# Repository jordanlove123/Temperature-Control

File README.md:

# Temperature Control
System for controlling temperature of an object to within 10 mK of a given setpoint.

DISCLAIMER: As is discussed below, some parts of the system will have to be designed by the user because they depend on the shape, size, and thermal mass of the object. This means that to a certain extent, performance is dependent on the user's design of these components, but I tried to include as many recommendations as possible for best practices.

## Setup

### Recommended installations
Before starting setup, there is software that is necessary to access some of the files in this repository:
* [Arduino IDE](https://www.arduino.cc/en/software/): Edit and upload Arduino code
* [KiCAD](https://www.kicad.org/download/): View and export PCB files
* [Prusa Slicer](https://www.prusa3d.com/page/prusaslicer_424/): Convert STL 3D models to gcode for a 3D printer
* [Realterm](https://sourceforge.net/projects/realterm/): Send serial commands and save serial data from Arduino to text file

These programs can all be downloaded for free.

### Manufacturing

#### Shield PCB
The PCB files can be found at [Manufacturing/Shield PCB](Manufacturing/ShieldPCB/). In order to get the manufacturing files, open the .kicad_pcb file and export according to what is necessary for your manufacturer of choice. If you don't have a manufacturer of choice, I recommend [JLCPCB](https://jlcpcb.com/). Once you have the board, assemble it according to the component labels in the .kicad_sch file. The complete list of necessary components can be found in the [bill of materials](Manufacturing/BOM.xlsx).

#### Container (optional)
If you have access to a 3D printer, I recommend printing the container found in [Manufacturing/Box](Manufacturing/Box). This can be done by opening the .stl files in Prusa Slicer and converting them to gcode:

Then export the gcode file and give it to your 3D printer:

#### Temperature Probe
This system uses two temperature sensors: one for the feedback loop that controls the temperature in addition to a heater, and one for independent monitoring of the temperature with a sensor outside the feedback loop. Because the configuration of these sensors and the heater will depend on the form factor of the object being temperature controlled, there is no case for them in this repository, but there are requirements for how it is built. The temperature sensors should be two 10k thermistors in a voltage divider as shown below:

<div align="center">
    
</div>

TEMP1 and TEMP2 are the two signal cables that will be connected to IN1 and IN2 on the shield, REF comes from the REF pin on the shield and is generated by the on-board 2.5V voltage regulator, and GND comes from one of the GND pins on the shield. Additionally, a heating resistor connected to the R6 pin header should be placed near the object being temperature controlled. If you're using the optional container, all of the wires in your case should be connected to a d-sub 9 connector so they can be plugged into the container. Some additional recommendations for configuration of the probe:

* Try to thermally isolate the sensor-heater-object system as best as you can with the case that you build. This will have the largest effect on the performance of the system.
* Place the temperature sensors far from the heater. This will ensure that you're measuring the actual temperature of the object, not just the temperature of the heater.
* Don't place the sensors too close to each other so you can see on the independent sensor if the object is being heated unevenly.
* Try to match the resistors in the voltage dividers as best as possible. This will ensure that the voltage you measure on both dividers is the same as long as the temperature is the same.

Because the performance is largely dependent on the probe setup, there are no guarantees that you will get mK-level stability if it isn't good enough. However, below you will find tools to assess the performance and potential flaws of your setup so you can iterate your design until it is good enough.

### Assembly
Connecting the shield PCB to the Arduino is very simple: just align the pins coming from the underside of the PCB with the input pins of the Arduino and connect them directly so the PCB is sitting on top of the Arduino. There should be an exact one-to-one match between PCB pins and Arduino pins. If you're using the optional container, use the following images as a reference to place the components within it correctly.

Box front:

<div align="center">
    
</div>

Box back:

<div align="center">
    
</div>

Box top:

<div align="center">
    
</div>

Use the following wiring diagram to make the necessary connections:

<div align="center">
    
</div>

WARNING: THE WALL PLUG CARRIES HIGH VOLTAGES WHEN CONNECTED. BE VERY CAUTIOUS WHEN WORKING WITH POWER CABLES AND DO NOT PLUG IN THE BOX UNTIL ALL THESE CABLES ARE SHRINK WRAPPED AND THERE IS NO EXPOSED METAL. PLUGGING IN WITHOUT TAKING THE CORRECT PRECAUTIONS COULD CAUSE HARM.

### Code
The Arduino code makes use of two custom libraries: AD7190 for interfacing with the ADC on the shield and PID for handling the feedback loop of the system. These two folders can be found in [Code/Libraries](Code/Libraries) and can be installed using the following steps:

* Save both folders as a zip file
* Open the Arduino IDE and select Sketch > Include Library > Add .ZIP Library
* Navigate to the location where your libraries are saved and select them

The code to be uploaded to the Arduino is found in [Code/Arduino](Code/Arduino)

## Usage

### Serial commands
The Arduino accepts a variety of commands to interface with the PID system, which are summarized in the table below:
| Command          | Arguments accepted             | Description                                                                                                 |
|:-----------------|:-------------------------------|:------------------------------------------------------------------------------------------------------------|
| p \[arg1\]       | arg1: double > 0               | Change the K<sub>p</sub> parameter of the PID system                                                        |
| i \[arg1\]       | arg1: double > 0               | Change the K<sub>i</sub> parameter of the PID system                                                        |
| d \[arg1\]       | arg1: double > 0               | Change the K<sub>d</sub> parameter of the PID system                                                        |
| heat \[arg1\]    | arg1: 0 or 1                   | Turn heater off (0) or on (1)<sup>1</sup>                                                                   |
| setp \[arg1\]    | arg1: double < 29              | Change the setpoint of the PID system                                                                       |
| verbose \[arg1\] | arg1: 0 or 1                   | Output control stats to serial port (see [Serial output](#serial-output))                                   |
| rstime           | none                           | Restart the timestamp at 0                                                                                  |
| sint \[arg1\]    | arg1: double                   | Set the integral term to a custom value<sup>2</sup>                                                         |
| save             | none                           | Save the current K<sub>p</sub>, K<sub>i</sub>, K<sub>d</sub>, and setpoint to EEPROM<sup>3</sup>            |

<sup>1</sup> This is implemented in practice by multiplying the heater output by arg1, so passing any other number will have the effect of changing the gain of the entire system

<sup>2</sup> Due to the anti-windup, if |arg1| > 10, it will be set to either -10 or +10

<sup>3</sup> When an Arduio program is running, variables are stored in program memory which is volatile, meaning it is lost when the Arduino loses power. However, the Arduino also has a non-volatile form of data storage called EEPROM, so if you want to move your controller and disconnect power you won't lose the parameters you found during tuning. This memory has a limited number of write cycles though, so use this command sparingly.

Due to an unknown bug in the Arduino code, commands need to be sent multiple times in quick succession in order for them to be properly received.

### Serial output

When verbose is set to true, data is output to the serial port in the following format:

**Timestamp &nbsp;&nbsp;&nbsp; Temperature voltage &nbsp;&nbsp;&nbsp; Independent sensor reading &nbsp;&nbsp;&nbsp; Error voltage &nbsp;&nbsp;&nbsp; Proportional term &nbsp;&nbsp;&nbsp; Integral term &nbsp;&nbsp;&nbsp; Derivative term &nbsp;&nbsp;&nbsp; Output power &nbsp;&nbsp;&nbsp; Output voltage to heater circuit**

### Tuning
DISCLAIMER: This is not necessarily the optimal tuning method, but just the one that I found works best for me. If you have another method that you prefer and you know it works better, go ahead and use it. This is just for a beginner to get a feel for tuning. However, I have found that some common tuning methods don't work very well, possibly because of some of the non-linearities in the system.

NOTE: There is a [jupyter notebook](Code/Data%20Analysis/data_analysis.ipynb) in Code/Data Analysis that can be used to help with tuning. If you would like to use your own analysis techniques, it is not required to use this notebook, however if you have your own analysis techniques in addition to those found in the notebook, you probably don't need this section anyway.

The notebook has 3 main cells that will be useful. The first one, third from the top, will just take your data and plot everything from the serial output on it's own axis for the entire dataset. This can be used to look at your data wholistically and to analyze long term stability. The next cell from the top will plot the last 150 seconds of data, and updates every second. This can be used if you want to see live-updating data and catch any large errors without having to wait to see everything at once. The last one is the PSA spectrum of the P, I, and D terms of the controller and the temperature data. This essentially shows you how much of each frequency is contained in the data, which is useful for reasons explained below.

#### Step response
When tuning, you will want to look at the step response of your system, which is just how it responds to an instantaneous change in the setpoint (In this case, moving it up). Do this by turning off the heater, waiting for the temperature to return to room temperature, then sending the command "sint 0" and turning the heater back on. The step response will be the temperature graph after turning the heat back on.

#### Recognizing issues
Once you get to the point of tuning the parameters of the system, you want to make sure the probe setup is good enough, because otherwise you're limited by the quality of your setup instead of the accuracy of the parameters. The main issue that you will run into with the probe setup is insufficient thermal isolation, which means surrounding air temperature is being factored into your measurement. Generally, the object being temperature controlled will have a much larger thermal mass than the surrounding air, so watch for large, quick changes in temperature. A normal time period for a temperature change depends on your thermal mass, but will typically be on the order of a couple minutes. If you see relatively large temperature changes happening in a matter of seconds, it's probably a probe issue rather than a parameter issue.

#### Step 0: The basics
Before starting, a general overview of PID. PID stands for proportional, integral, derivative, and controls a system using exactly those things. It takes as input the error between the setpoint and the actual temperature and outputs the negative sum of the integral of the error, derivative of the error, and exact error all scaled by constants, called the gains. The proportional term just pushes the temperature towards the setpoint. This might be enough in some cases, but think about what would happen if the error were 0 and the temperature was above room temperature. A controller with only the proportional term would not be doing anything to keep the temperature above room temperature because K*0 = 0 so it would output 0. This means any controller with only the proportional term will have some steady state error. This is where the integral term comes in. If there is any steady state error, the integral term will accumulate over time, pushing the temperature towards the setpoint. The speed that it accumulates is dictated by the integral gain. Notably, too high of a proportional gain or integral gain will cause oscillations, which are not what we want. This is where the derivative term comes in. It can be thought of as predicting the future; if the derivative is positive, the temperature will probably go up, and so the derivative term preemptively reduces the output power to reduce this change. Such a term will provide damping of oscillations, and that is its job.

#### Step 1: Picking a setpoint
Before doing any tuning, figure out the ambient temperature of the object being temperature controlled using the system. The system guarantees high precision, but not high accuracy, so doing this will give you a frame of reference for what the temperature actually is. Once you've done this, set the setpoint. It can be whatever you want but is bounded on both sides by two factors: the bottom end is about 2-3 <sup>o</sup>C above room temperature since the system has no cooler so ambient temperature is used to cool it, and the upper end is limited by your heater's power output. This depends on the resistance of the heater and the input voltage that you use (12V if you use the optional container with no modifications).

#### Step 2: Finding proportional gain
The next step after setting the setpoint is to find K<sub>p</sub>, the proportional gain of the system. To find the proportional gain, just pick a number to start. If the step response goes past the setpoint, reduce it by half until it doesn't. Then, slowly turn it up and watch the step response each time you change it. Once it is settling close to the setpoint, but slightly below, move on to step 3.

#### Step 3: Finding integral gain
First, cut your proportional gain in half, and then pick a number for your integral gain. It will probably be much smaller than the proportional gain you found. If the oscillations are centered above the setpoint while it settles, turn the integral gain down. If below, do the opposite. Once the oscillations are centered approximately at the setpoint, move on to the next step.

#### Step 4: Finding derivative gain
This step is pretty simple, just turn up the derivative gain until the oscillations are damped as much as is necessary for your purposes. The higher it is, the more damped they will be. If your derivative gain gets too high, the integral term might accumulate more than it was before because the derivative term slows the original ascent to the setpoint, so you'll need to turn down the integral gain slightly. Once you've finished finding the parameters, a good step response will look something like this:

#### Step 5: Fine tuning the parameters
The above steps help with the original settling to the setpoint, but in order to get the best steady state performance, the parameters need to be tuned a little more. To do this, take about 12 hours of data after the temperature has settled and look at the PSA spectrum. An ideal spectrum will look like this:

<div align="center">
    
</div>

Note the integral term is the strongest at lower frequencies, then the proportional term takes over in the middle frequencies, and finally the derivative term takes over at high frequencies. It will also have two points where all terms will start to roll off: one is the natural frequency of your system; the temperature can't change any faster than that, and the other is due to a filter in the feedback loop. Just ignore these and look at the general shape. If the shape doesn't look like this, you can move each term up by multiplying it by a scaling factor, and move it down by dividing by a scaling factor. Scale the parameters appropriately and they should then be optimal.

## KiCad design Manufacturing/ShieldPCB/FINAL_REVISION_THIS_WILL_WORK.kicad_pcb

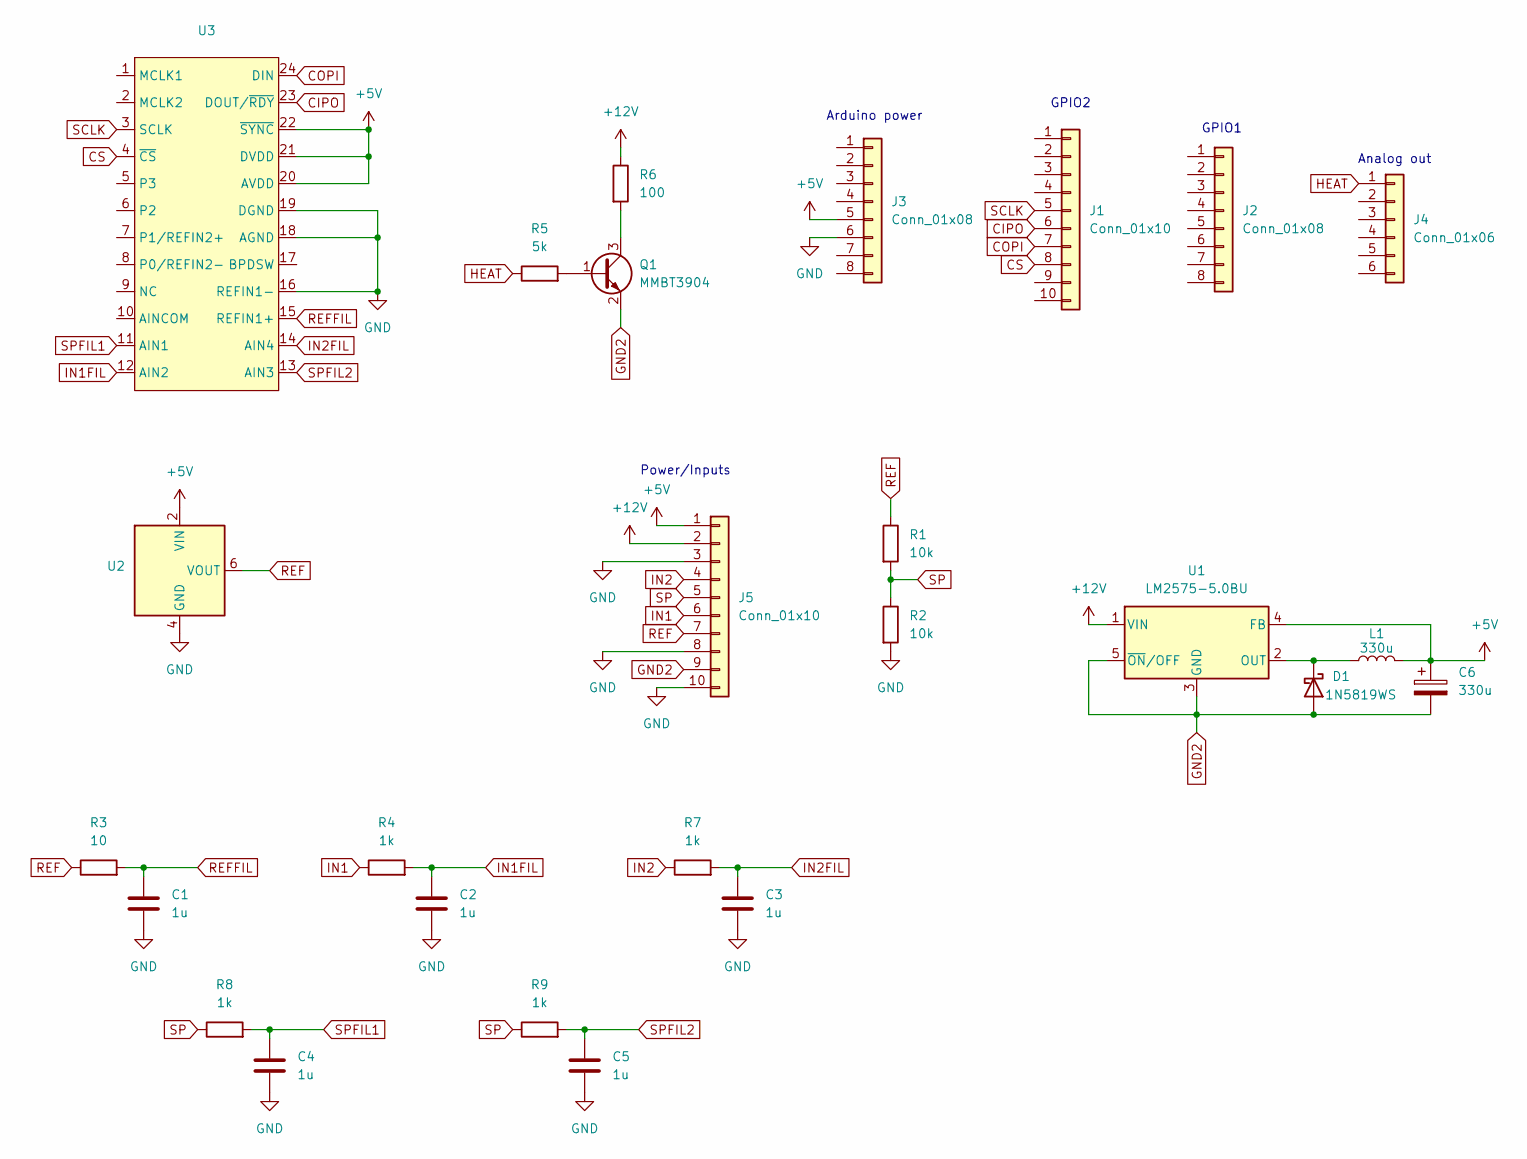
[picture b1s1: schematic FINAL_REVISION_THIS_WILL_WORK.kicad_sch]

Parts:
C1, C2, C3, C4, C5: 1u; C_0805_2012Metric
C6: 330u; C_Elec_6.3x7.7
D1: 1N5819WS; D_SOD-123
J1: Conn_01x10; PinSocket_1x10_P2.54mm_Vertical
J2, J3: Conn_01x08; PinSocket_1x08_P2.54mm_Vertical
J4: Conn_01x06; PinSocket_1x06_P2.54mm_Vertical
J5: Conn_01x10; PinHeader_1x10_P2.54mm_Vertical
L1: 330u; L_1812_4532Metric
Q1: MMBT3904; SOT-23
R1, R2: 10k; R_0805_2012Metric
R3: 10; R_0805_2012Metric
R4, R7, R8, R9: 1k; R_0805_2012Metric
R5: 5k; R_0805_2012Metric
R6: 100; PinHeader_1x02_P2.54mm_Vertical
U1: LM2575-5.0BU; TO-263-5_TabPin3
U2: SOIC-8_3.9x4.9mm_P1.27mm
U3: TSSOP-24_4.4x7.8mm_P0.65mm

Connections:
+5V: C6.1, J3.5, J5.1, L1.2, U1.4 (FB), U2.2 (VIN), U3.20 (AVDD), U3.21 (DVDD), U3.22 (~SYNC)
+12V: J5.2, R6.1, U1.1 (VIN)
CIPO: J1.6, U3.23 (DOUT/~RDY)
COPI: J1.7, U3.24 (DIN)
CS: J1.8, U3.4 (~CS)
GND: C1.2, C2.2, C3.2, C4.2, C5.2, J3.6, J5.3, J5.8, J5.10, R2.2, U2.4 (GND), U3.16 (REFIN1-), U3.18 (AGND), U3.19 (DGND)
GND2: C6.2, D1.2 (A), J5.9, Q1.2 (E), U1.3 (GND), U1.5 (~ON/OFF)
HEAT: J4.1, R5.1
IN1: J5.6, R4.1
IN1FIL: C2.1, R4.2, U3.12 (AIN2)
IN2: J5.4, R7.1
IN2FIL: C3.1, R7.2, U3.14 (AIN4)
unnamed: D1.1 (K), L1.1, U1.2 (OUT)
unnamed: Q1.1 (B), R5.2
unnamed: Q1.3 (C), R6.2
REF: J5.7, R1.1, R3.1, U2.6 (VOUT)
REFFIL: C1.1, R3.2, U3.15 (REFIN1+)
SCLK: J1.5, U3.3 (SCLK)
SP: J5.5, R1.2, R2.1, R8.1, R9.1
SPFIL1: C4.1, R8.2, U3.11 (AIN1)
SPFIL2: C5.1, R9.2, U3.13 (AIN3)

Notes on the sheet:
Arduino power
GPIO2
GPIO1
Analog out
Power/Inputs

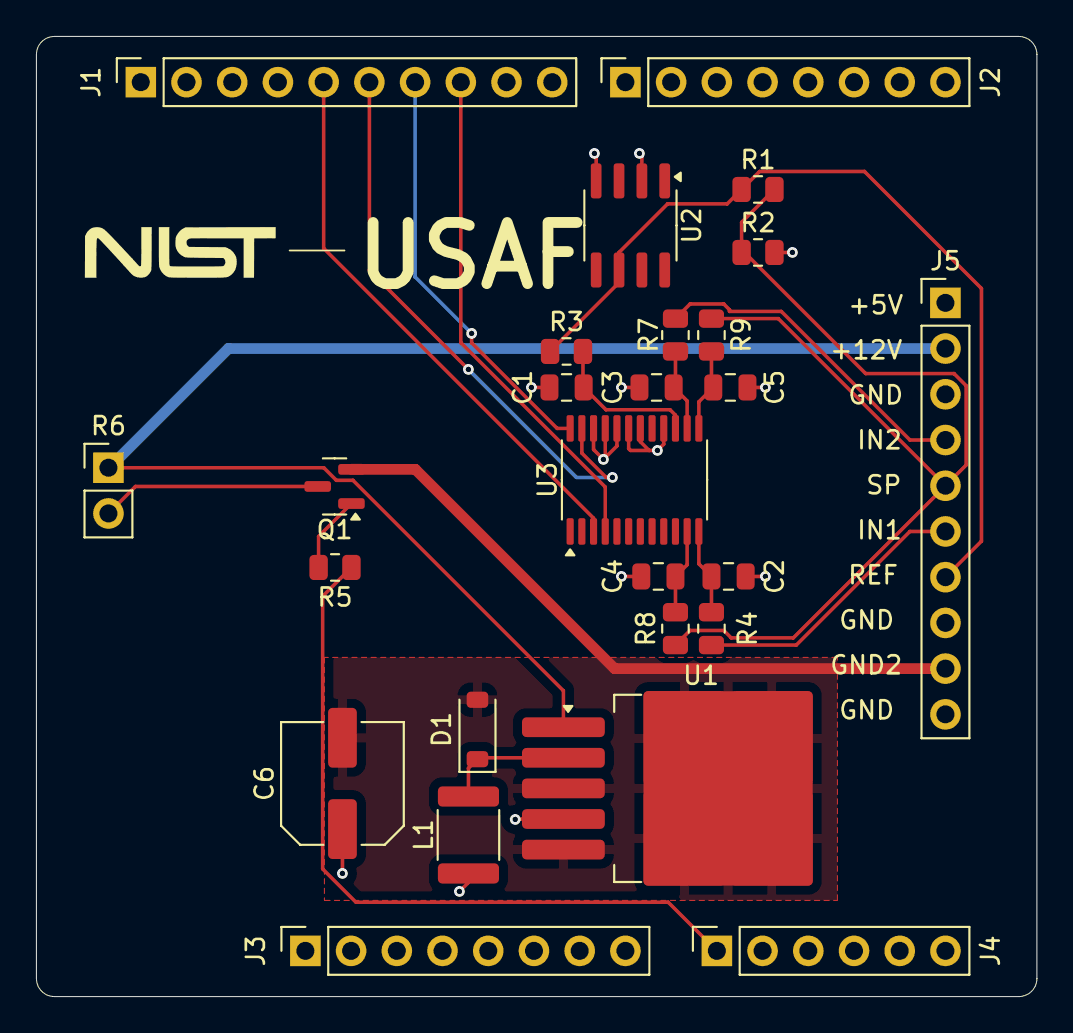
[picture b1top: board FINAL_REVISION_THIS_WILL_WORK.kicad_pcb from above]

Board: 4 copper layers, 55.6 x 53.3 mm, 26 parts (0 on the bottom side), 21 nets.

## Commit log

2025-08-18 fix typos and working in readme
2025-08-18 udpate readme
2025-08-18 remove output from cells in jupyter notebook
2025-08-18 add BOM
